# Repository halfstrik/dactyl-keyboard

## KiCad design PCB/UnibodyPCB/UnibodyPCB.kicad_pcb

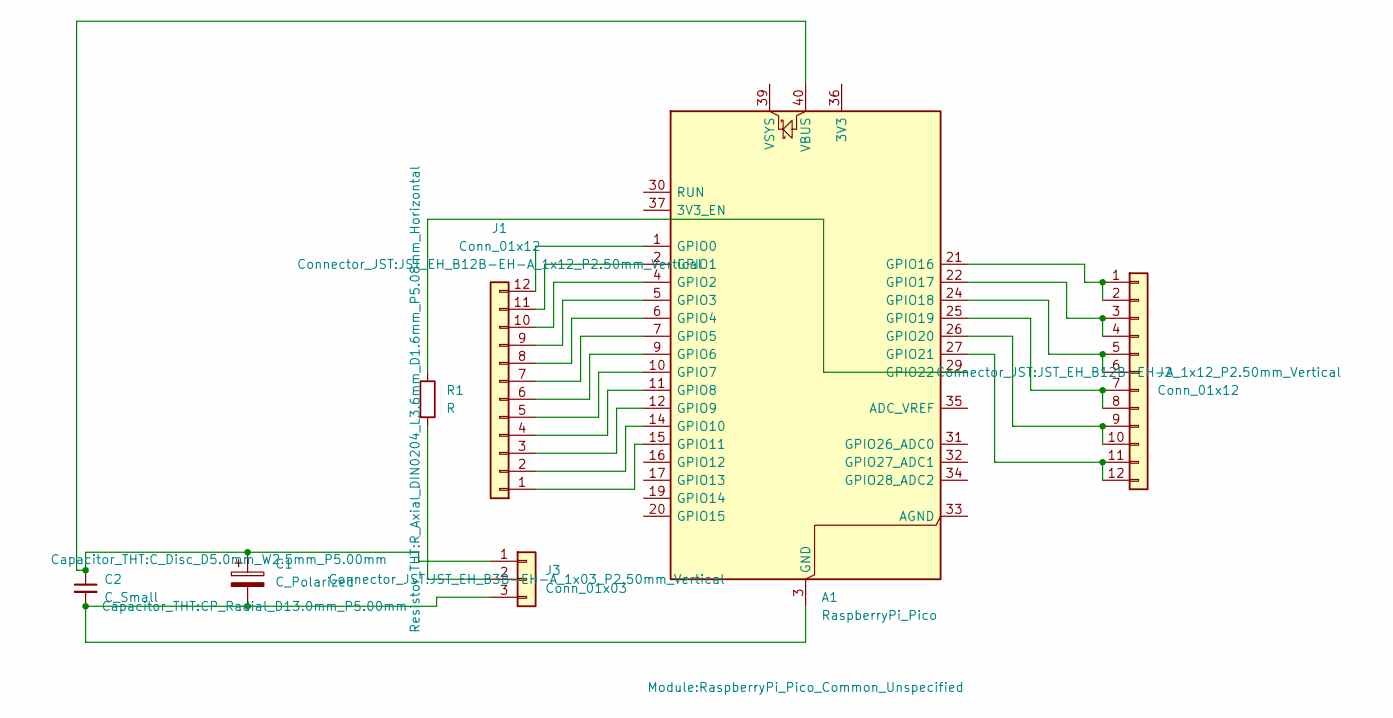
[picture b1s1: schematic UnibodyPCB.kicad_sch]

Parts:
A1: RaspberryPi_Pico; RaspberryPi_Pico_Common_Unspecified
C1: C_Polarized; CP_Radial_D13.0mm_P5.00mm
C2: C_Small; C_Disc_D5.0mm_W2.5mm_P5.00mm
J1, J2: Conn_01x12; JST_EH_B12B-EH-A_1x12_P2.50mm_Vertical
J3: Conn_01x03; JST_EH_B3B-EH-A_1x03_P2.50mm_Vertical
R1: R; R_Axial_DIN0204_L3.6mm_D1.6mm_P5.08mm_Horizontal

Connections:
unnamed: A1.1 (GPIO0), J1.12
unnamed: A1.2 (GPIO1), J1.11
unnamed: A1.4 (GPIO2), J1.10
unnamed: A1.5 (GPIO3), J1.9
unnamed: A1.6 (GPIO4), J1.8
unnamed: A1.7 (GPIO5), J1.7
unnamed: A1.9 (GPIO6), J1.6
unnamed: A1.10 (GPIO7), J1.5
unnamed: A1.11 (GPIO8), J1.4
unnamed: A1.12 (GPIO9), J1.3
unnamed: A1.14 (GPIO10), J1.2
unnamed: A1.15 (GPIO11), J1.1
unnamed: A1.21 (GPIO16), J2.1, J2.2
unnamed: A1.22 (GPIO17), J2.3, J2.4
unnamed: A1.24 (GPIO18), J2.5, J2.6
unnamed: A1.25 (GPIO19), J2.7, J2.8
unnamed: A1.26 (GPIO20), J2.9, J2.10
unnamed: A1.27 (GPIO21), J2.11, J2.12
unnamed: A1.29 (GPIO22), R1.1
unnamed: A1.40 (VBUS), C1.1, C2.1, J3.1
unnamed: J3.2, R1.2
unnamed: A1.3 (GND), A1.8 (GND), A1.13 (GND), A1.18 (GND), A1.23 (GND), A1.28 (GND), A1.38 (GND), C1.2, C2.2, J3.3

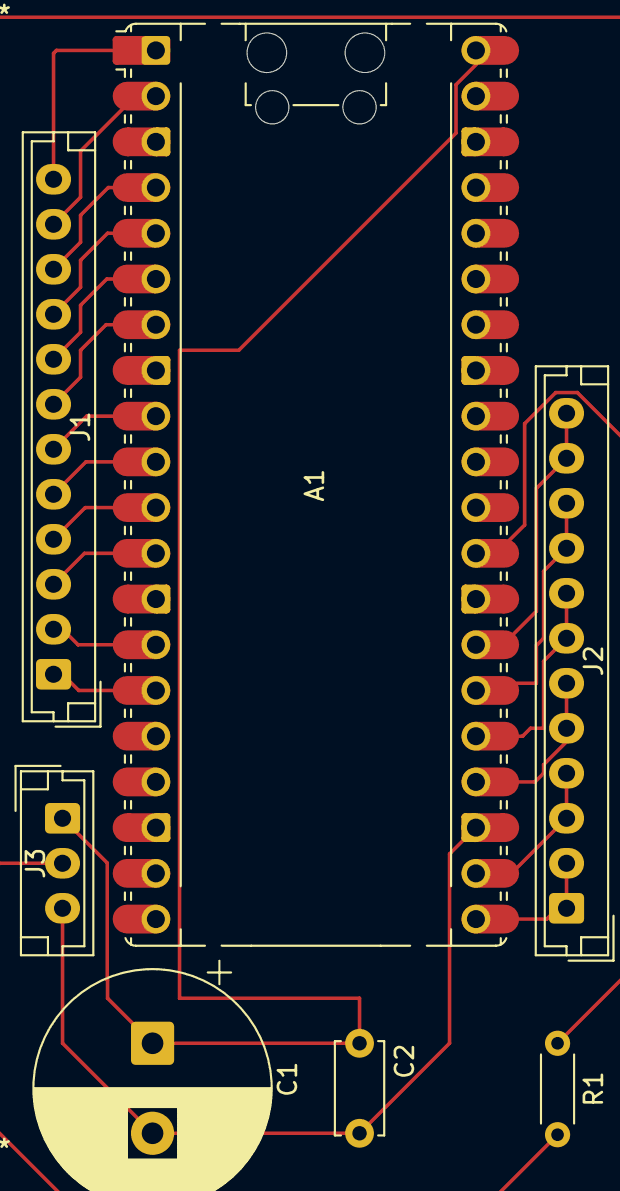
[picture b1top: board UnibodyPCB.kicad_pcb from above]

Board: 2 copper layers, 7 parts (0 on the bottom side), 22 nets.

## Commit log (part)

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2025-09-07 Remove under pinky key as it's hard to reach. Reduce wall heigh as it will be hidden. Use keycap with notches. Reduce generated files for faster debug.
2025-10-08 Modify shift column keys to be 1.5 width, reduse border to fit new case better
2025-10-08 Improve thumb cluster positioning, make it stick more outwards and less up
2025-10-09 Few more adjustments to better fit the shape
2025-10-09 One more little tweak, move thumbs a bit more down and inwards
2025-10-10 Move thumbs a bit closer, add buffed caps for cutting
2025-10-10 Reduce walls, only use to get strength, no overhang
2025-10-31 Added simple module frame to replicate keyboard frame in Clojure.
2025-10-31 Improve base dimensions
2025-11-01 Draft, added right sphere for a well, still need adjustment
2025-11-02 Added inner cut to form top plate walls and define thickness
2025-11-04 Added simple keycaps, not aligned yet
2025-11-04 Uncomment right wall, move it a bit
2025-11-04 Make Kinesis-like 1.5 keys
2025-11-04 Improve keycaps for better cut
2025-11-04 Uncomment left half
2025-11-06 Align keys (more or less)
2025-11-06 Added cut for keys, while making keys more square
2025-12-02 Make thumb cluster more flat Rolled back keycaps
2025-12-02 Improve key-well sphere with a hull
2025-12-02 Introduce back sphere so that whole case is smaller and more elegant
2025-12-02 instead of using expensive minkovski, us paired hulls, much cheaper
2025-12-02 Add key support and optional caps
2025-12-03 Add shift column pillar
2025-12-03 Add plus column pillar
2025-12-06 Add five column pillar
2025-12-06 Add home key pillar (last of 4)
2025-12-06 Cut main case in half and separate top section by substruction
2025-12-06 Added glue helper in the middle to the right part
2025-12-06 Add indent for a screw Add separate mirror for left well
2025-12-06 Fix mirror
2025-12-07 Improve key cut
2025-12-07 Added left top panel
2025-12-08 Improve glue reinforcement plates for better adhesion
2025-12-08 Add mounts for the bottom plate
2025-12-08 Alter top part to better fit bottom Start working on bottom part, WIP, made outline
2025-12-09 An attempt to make bottom WIP
2025-12-09 Refactror, add cable cat cylinder
2025-12-09 Added thumb spacer to get more real estate for thumbs
2025-12-09 Add bottom inline and substruct it from outline attempt
2025-12-09 Fix rendering
2025-12-09 Bottom box ready
2025-12-09 Bottom box ready, add stl import for faster future work
2025-12-09 Re-render stl
2025-12-12 Add legs, very simple implementation
2025-12-12 Added top cover stl, aligned glue support
2025-12-13 Added bottom mount pillars
2025-12-13 Added border holders for the bottom
2025-12-13 Added glue for the right part, rendering expensive common bottom part...
2025-12-13 Generate final right (left) bottom case, ready to print!!!
2025-12-13 Added left part of the case(really right, need to revert them)
2025-12-13 Add border support and some screw holes for top section
2025-12-13 Finalize right up case
2025-12-14 Finalize right top case
2025-12-14 Add cuts in support pillars
2025-12-14 Added left case
2025-12-14 Complete right key well with border and cuts
2025-12-14 Readded the right model for right well
2025-12-15 Update right well, move wall out. Added left well
2025-12-17 Lower main sphere by 4 (mm) so that tumb keys stick out more, also add additional support for key well cluster for better stability
2025-12-17 Make cut for lower and upper sides even (11 instead of 13)
2025-12-18 Adjust glue attachments for raft base (make them shorter to fit the printer)
2025-12-19 Increase main cylinder to get to the corner Increate wire cut cylinder to look more ecstatic Move leg a bit out for better balance
2025-12-19 Finish bottom part
2025-12-21 Add Pico mount with circuit
2025-12-21 ALso added re-draw for case stls
2025-12-29 WIP; Added cut for key number 3
2025-12-29 Improve keys cuts + move well few mm to the right (so index finger won't clash with well wall)
2025-12-29 Adjust for better thumbs cut
2025-12-30 Introduce new slicing for the up part, slice into 3 parts instead of two, to hide seam in the middle and add stability using well and glue
2025-12-30 Fix well support for right most top part, eliminated most generated supports
2025-12-30 Added new connector for the corner, but still need to do proper substraction, need to create negative of the bottom
2025-12-30 Finish with right most case part, minimal supports
2025-12-31 Refactor, remove some dead code
2025-12-31 Added middle well support on both sides without autogenerated supports. Updated dactyl-top-right.stl
2025-12-31 Finish with middle part
2025-12-31 Simplify bottom shell rendering
2026-01-01 Fix bottom glue and holders
2026-01-01 Refactor code
2026-01-01 Added usb cut
2026-01-01 remove comments
2026-01-01 Fixed two support pillars for well (shift and plus)
2026-01-02 Big improvments with well, still WIP
2026-01-02 Finish wells
2026-01-02 Finish wells - left
2026-01-02 Fix minor issues with key well
2026-01-02 Improve sphere for better print
2026-01-03 Finish with the well, ready to print
2026-01-04 Improve well and backplate connection
2026-01-04 Final well improvements and render
2026-01-04 Adjust cuts in top plate
2026-01-04 Complete middle up case
2026-01-05 Update bottom case
2026-01-06 Added holes for bottom frame for screws
2026-01-06 Fix left bottom case
2026-01-08 Updated frame to count all issues during the initial print
2026-01-08 Re render wells
2026-01-08 Redo usb mount
2026-01-08 Fix bug in mount
2026-01-25 Raise top thumb keys by 3mm so normal keys will fit instead of custom Kinesis keys
2026-01-25 Increase home mount on the well side, eliminate it on top panel
2026-01-25 Revert changes, make pillar for home taller
2026-01-25 A few adjustments for home mount
2026-01-25 Improve home pillow adhesion
2026-01-25 Improve dimensions of bottom inline so the case will fully close
2026-01-25 Remove unused code
2026-01-29 Re-generate stls, remove unused empty lines
2026-02-27 Added ramp for LED strip
2026-03-02 Added PCB design for our main PCB
2026-03-03 Update kikad model
2026-03-03 Make rounded corners
2026-03-03 Added small gap so that top won't stick out
2026-03-04 Re-do pi mount on the bottom
2026-03-04 (unionii Update Pi mount, we will remove extra clip beneth it
2026-03-04 Make corner edges rounded, increase usb cut
2026-03-04 Fix bottom
2026-03-09 Commiting STLs
2026-03-09 WIP make skirt for the top
2026-03-10 Added cut for the skirt Added rear bottom support for outer peice
2026-03-10 Update stls
2026-03-13 Make cut for RGB LED strips in the bottom
2026-03-14 Added simple glue supports
2026-03-14 Make pico mount 0.5 mm lower, we can add washers if needed higher. Reduce holes diameter
2026-03-16 Fix top glue press
2026-03-16 Make thumb led holder a bit smaller, to avoid intersecting switches/diods/wires
2026-03-16 Design USB hole decorative plug
2026-03-16 Slight adjustment
2026-03-20 Fix USB C plug cover
2026-03-20 Increase screw holse so we don't need to drill them before inserting m3 bolt
2026-03-20 Update PCB files - mounting holes moved
2026-03-20 Improve thumbs key spacing, keys no longer touching
2026-03-20 Improce keys cut, so that we don't need to cut printed part
2026-03-20 Make proper cuts for all keycaps, increate last hole radius
2026-03-20 Cut top notch
2026-03-21 Fix well "+" mount
2026-03-22 Fix glue notch not to interfere with middle part
2026-03-22 Add hotswap sockets support
2026-03-27 WIP add micro usb cut
2026-03-27 Mirrored pins
2026-03-31 Improve micro usb plug
2026-03-31 Add pin housing cuts
2026-03-31 First attempt to add hotswap sockets support
2026-03-31 Adjust dimensions for a better fit
2026-03-31 Added hotswap support prototype
2026-03-31 Added two rows sockets support prototype
2026-04-01 WIP, adding mold for well to fit casing
2026-04-02 Made working hotswap sockets support for well
2026-04-03 Improve geometry of connections
2026-04-03 Improve cuts
2026-04-03 Improve joints
2026-04-03 Improve thumbs, just joints are needed
2026-04-03 Final edits
2026-04-03 Final fixes
2026-04-04 More fixes for artifacts
2026-04-06 WIP, code duplication to produce left well with hotswap sockets. Needs to be refactored
2026-04-09 Improvments for hotswap insert, but too thin. WIP
2026-04-09 Greatly improved insert, thin bottom with thicker round hanging parts
2026-04-09 Finish both left and right inserts
2026-04-14 Move hotswap mount into it's own dir, as it's getting big
2026-04-16 Increased bottom cover by 1mm in circle and 0.5mm in the bottom to make it to close better
2026-04-16 Improve wells for hotswap switches to fit under - and + top edge buttons
2026-04-17 Adjust glue supports for a new back plate
2026-04-18 Improve wells, still wip, need better cylinder joint
2026-04-18 Improve cylinder connection
2026-04-18 Better parametrize wells, reduce duplication
2026-04-23 Work on bottom support, next fix connections
2026-04-23 Incorporate initial rgb support for better led adhision and more consistent shape
2026-04-23 Slight adjustments for left notch
2026-04-23 Fix for left well insert
2026-05-02 Back-propagate well cylinder closure
2026-05-02 Fix + key support
2026-05-02 Remove leds mount, as we trying different lights approach
2026-05-02 First multicolor attempt, added a space to insert logo as well
2026-05-03 Added very text simple logo
2026-05-05 Make better corners on left and right by adding yet another sphere
2026-05-08 Added led housing (naive, shine through). Improve USB plug
2026-05-08 Bring back micro usb plug
2026-05-08 Move usb plug into separate file together with micro usb
2026-05-08 Modified the Clojure code to tweak the physical case design, specifically increasing the size of a supporting cube and adding a new subtraction (cut) to the geometry. (gemini:) )
2026-05-25 Use single front mount as oppose to double to allow transparent cut for lights
2026-05-26 Improve mounting hole for pcb
2026-05-26 Improve top right part to not interfear with bottom. Added connection teeth support on the rear.
2026-05-26 Added teeth connections for middle part, holds very strong
2026-05-27 Improve bottom, make side notch better adhere and deepened legs by 1mm
2026-05-27 Fix bottom left to add multicolor and fix support issue for glue joints
2026-05-27 Clear well for inner lock
2026-06-01 Improve on logo generation and add holes for back side engravings/info
2026-06-03 Update left well stls
